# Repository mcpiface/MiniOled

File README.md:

# MiniOled

## Python setup

sudo apt-get update
sudo apt-get install build-essential python-dev python-pip
sudo pip install RPi.GPIO

/// ----------------------------
Didn't do:

sudo apt-get install python-imaging python-smbus

sudo apt-get install git
git clone https://github.com/adafruit/Adafruit_Python_SSD1306.git
cd Adafruit_Python_SSD1306
sudo python setup.py install
/// ----------------------------

SSD1306 Driver from Adafruit:

https://github.com/adafruit/Adafruit_Python_SSD1306

sudo python -m pip install --upgrade pip setuptools wheel
sudo pip install Adafruit-SSD1306

--

Demo:

git clone https://github.com/adafruit/Adafruit_Python_SSD1306.git
cd Adafruit_Python_SSD1306/examples/stats.py

----------------

Check for I2C display:
sudo apt-get install i2c-tools
sudo i2cdetect -y 1

Expect address: 3c

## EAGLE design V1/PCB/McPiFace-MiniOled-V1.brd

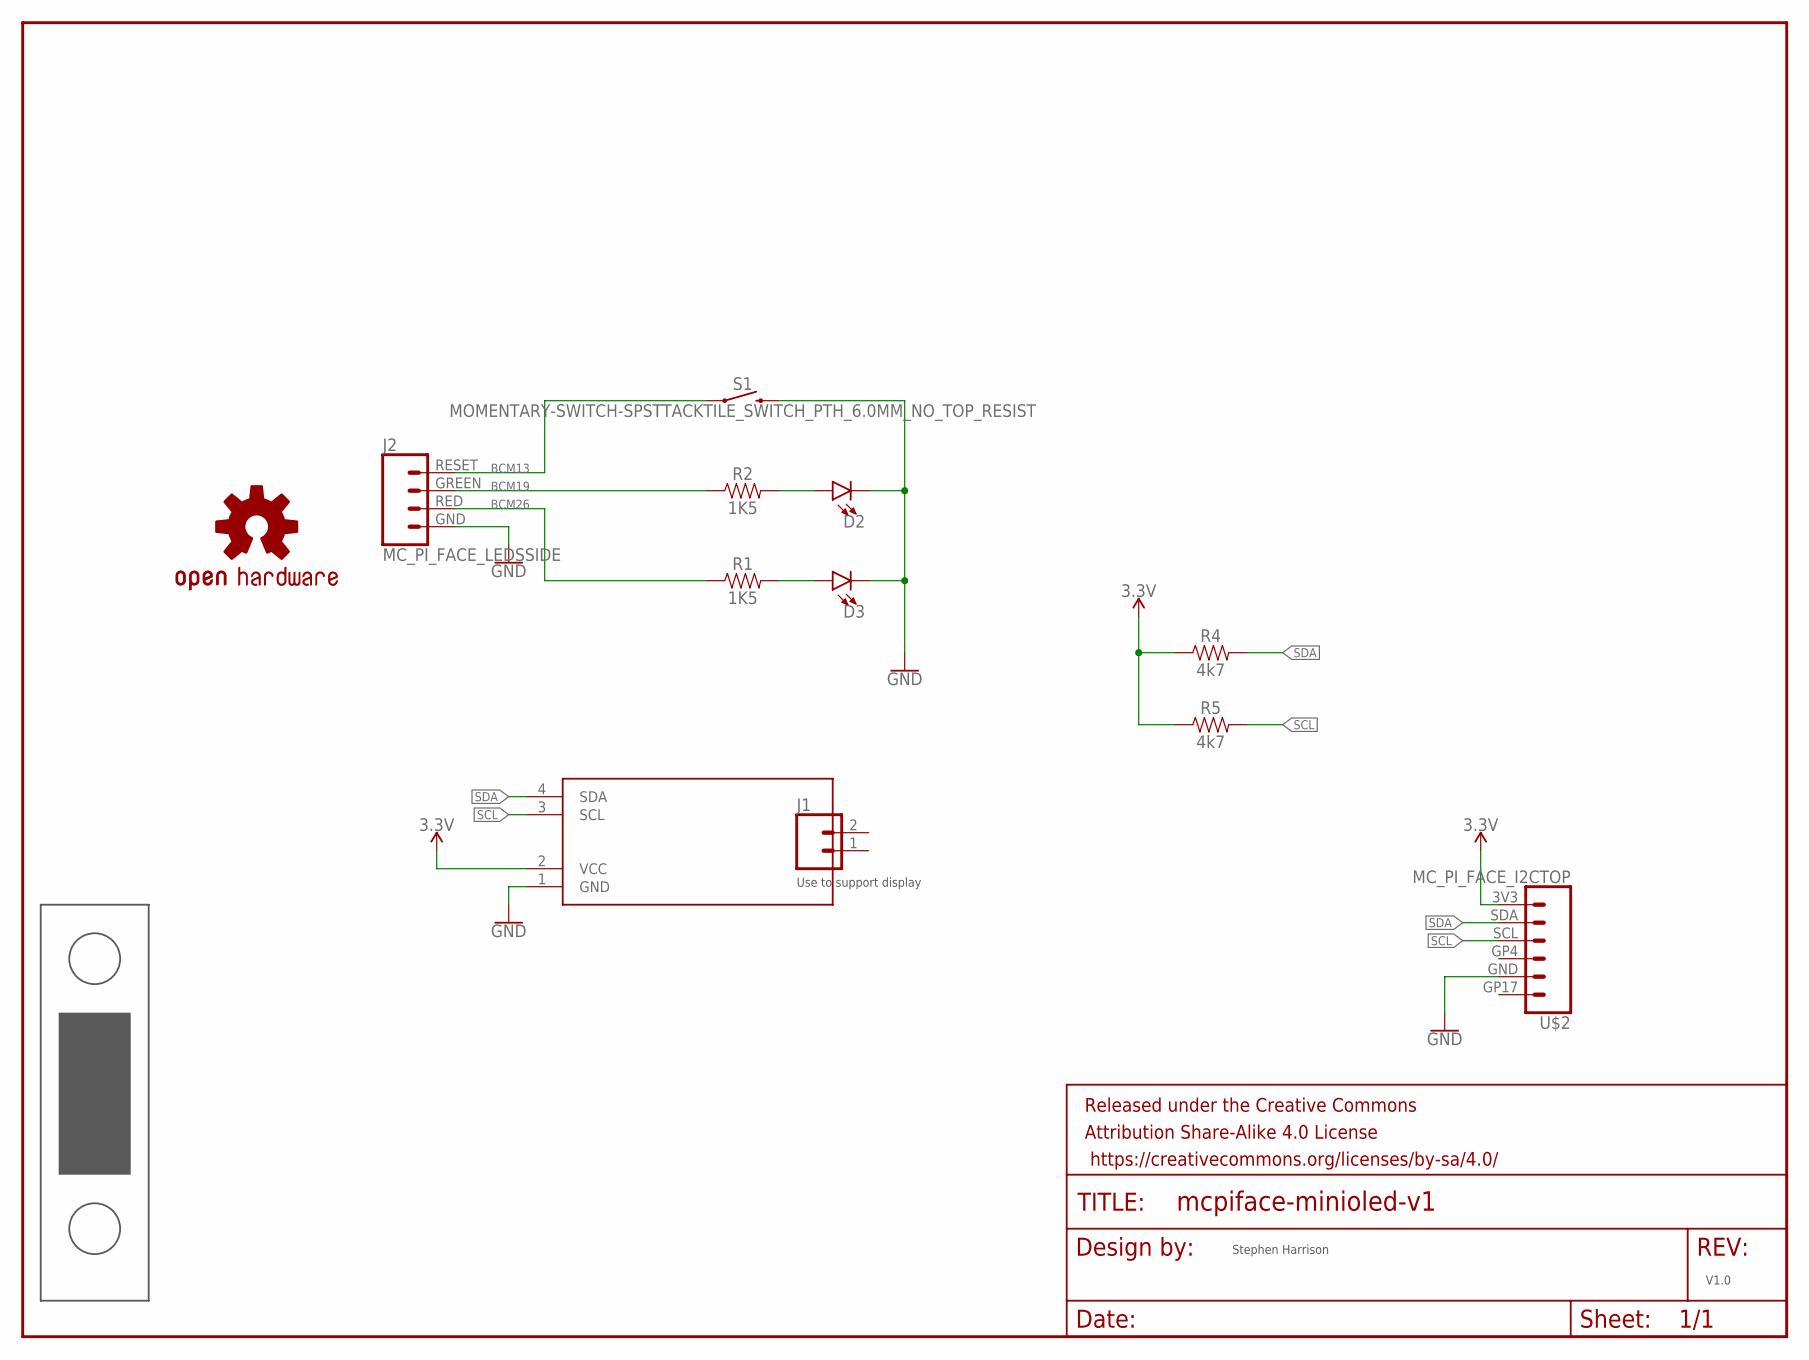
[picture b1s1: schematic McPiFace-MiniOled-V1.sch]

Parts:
D2: LEDLED-1206-BOTTOM-2.0MM-GREEN; LED-1206-BOTTOM-2.0MM
D3: LEDLED-1206-BOTTOM-2.0MM-RED; LED-1206-BOTTOM-2.0MM
DISPLAY: DISPLAY0.91_INCH_DISPLAY; I2C_DISPLAY_0.91_INCH
FRAME1: FRAME-LETTER; CREATIVE_COMMONS
J1: CONN_021X02_NO_SILK; 1X02_NO_SILK
J2: MC_PI_FACE_LEDSSIDE; JST-4-SH-1.0MM-SIDE
LOGO1: OSHW-LOGOL; OSHW-LOGO-L
R1, R2: 1K5; 0805
R4, R5: 4k7; 0805
S1: MOMENTARY-SWITCH-SPSTTACKTILE_SWITCH_PTH_6.0MM_NO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; TACTILE_SWITCH_PTH_6.0MM_NO_TOP_RESIST
U$1: MC_PI_FACE_JOINT
U$2: MC_PI_FACE_I2CTOP; JST-6-SH-1.0MM-TOP

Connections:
3.3V: DISPLAY.2 (VCC), R4.1, R5.1, U$2.3V3
BCM13: J2.RESET, S1.1
BCM19: J2.GREEN, R2.1
BCM26: J2.RED, R1.1
GND: D2.C, D3.C, DISPLAY.1 (GND), J2.GND, S1.3 (2), U$2.GND
unnamed: D3.A, R1.2
unnamed: D2.A, R2.2
SCL: DISPLAY.3 (SCL), R5.2, U$2.SCL
SDA: DISPLAY.4 (SDA), R4.2, U$2.SDA

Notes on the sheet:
Use to support display
Stephen Harrison
V1.0

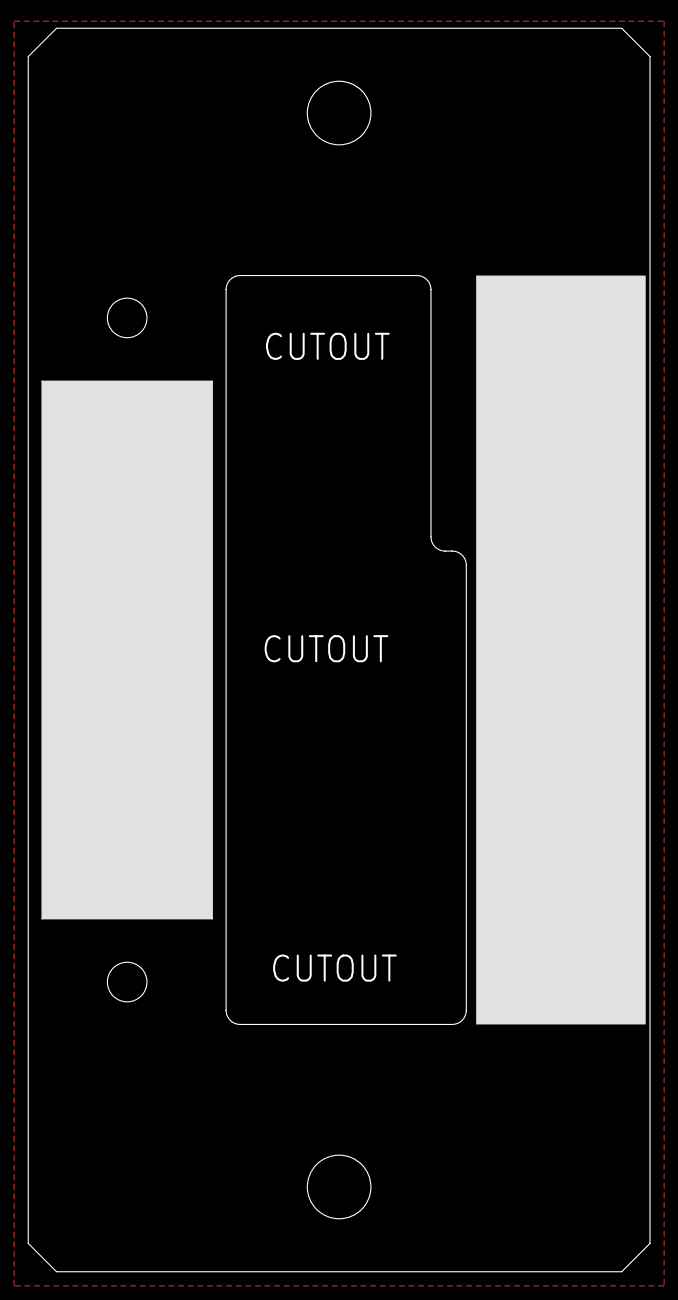
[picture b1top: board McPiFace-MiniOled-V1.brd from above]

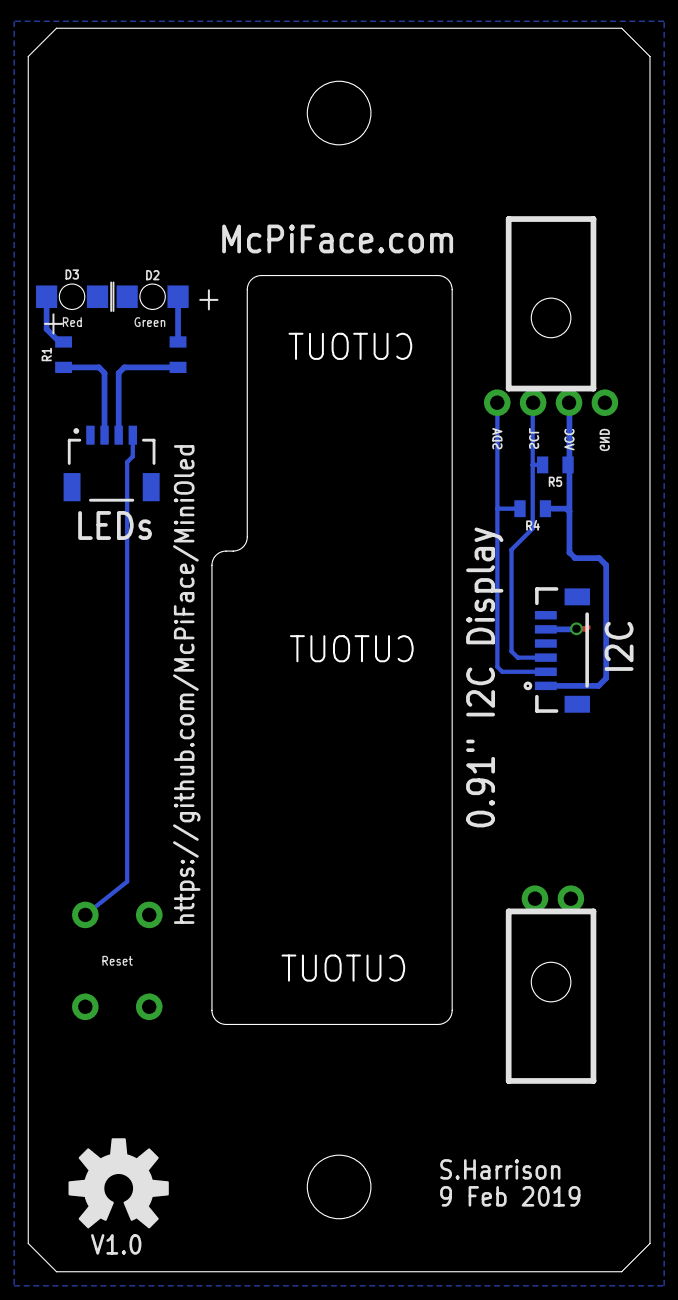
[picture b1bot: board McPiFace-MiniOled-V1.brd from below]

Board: 2 copper layers, 44.0 x 88.0 mm, 14 parts (9 on the bottom side), 9 nets.

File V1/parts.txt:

Partlist

Exported from McPiFace-MiniOled-V1.brd at 15/02/2019 19:13

EAGLE Version 7.4.0 Copyright (c) 1988-2015 CadSoft

Assembly variant: 

Part     Value                                                        Package                                Library             Position (mm)         Orientation

D2                                                                    LED-1206-BOTTOM-2.0MM                  ThingySticks        (35.2 69)             MR180
D3                                                                    LED-1206-BOTTOM-2.0MM                  ThingySticks        (40.9 69)             MR0
DISPLAY  DISPLAY0.91_INCH_DISPLAY                                     I2C_DISPLAY_0.91_INCH                  ThingySticks        (1 63)                R270
J1                                                                    1X02_NO_SILK                           SparkFun-Connectors (5.6 26.4)            R0
J2       MC_PI_FACE_LEDSSIDE                                          JST-4-SH-1.0MM-SIDE                    McPiFace            (38.1 59.2)           MR0
R1       1K5                                                          0805                                   SparkFun-Resistors  (41.5 64.9)           MR90
R2       1K5                                                          0805                                   SparkFun-Resistors  (33.4 64.9)           MR90
R4       4k7                                                          0805                                   SparkFun-Resistors  (8.3 54)              MR180
R5       4k7                                                          0805                                   SparkFun-Resistors  (6.7 57.1)            MR180
S1       MOMENTARY-SWITCH-SPSTTACKTILE_SWITCH_PTH_6.0MM_NO_TOP_RESIST TACTILE_SWITCH_PTH_6.0MM_NO_TOP_RESIST ThingySticks        (37.7 22)             R270
U$2      MC_PI_FACE_I2CTOP                                            JST-6-SH-1.0MM-TOP                     McPiFace            (6.1 44)              MR90

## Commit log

2019-02-09 V1 Mini Oled front panel.
2020-01-12 V2 for the Pi 4.
2020-01-12 Docs update.

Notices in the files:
parts and their libraries:
SparkFun-Aesthetics: Licensing: Creative Commons ShareAlike 4.0 International - https://creativecommons.org/licenses/by-sa/4.0
SparkFun-Aesthetics: Released under the Creative Commons Attribution Share-Alike 4.0 License
SparkFun-Aesthetics: https://creativecommons.org/licenses/by-sa/4.0
